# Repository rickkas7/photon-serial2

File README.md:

# Serial2 on the Particle Photon

Normally, the Particle Photon has one UART hardware serial port (Serial1) and the USB serial port (Serial). There is another hardware UART serial port (Serial2), but getting to it is a pain. I don't recommend using it. 

Serial2 shares the same pins as the RGB status LED. This means that you have to disable to status LED. This will make debugging a pain in the future. If your code is running, you can mirror the status LED on another LED. Unfortunately that doesn't work when your code is not running, which is really when you need the status LED. Plus, you need to do soldering and remove some SMD resistors from the Photon. 

Anyway, you have been warned. Here we go!

## Making bottom connections 

Here's the bottom of the Photon (USB connector on the right).

You need to make connections to pins 28 and 29 (the serial port) and optionally pin 27 (red LED). By doing all three, you can attach an external RGB LED to these pins, which may be helpful for debugging.

I used three female header sockets. You may prefer to use a different type of connector. Also, I decided that the pins should be mounted on the USB side, to keep the metal from the connectors out of the keep-away zone under the antenna.

Here is is after soldering the leads in place:

- White Wire: 28 Green LED/TX
- Purple Wire: 29 Blue LED/RX
- Brown Wire: 27 Red LED

I used epoxy to glue the headers in place. This was more difficult and messier than I anticipated.

There is a much better way of doing this at the end of the document!

## Testing out the LED

One advantage of making all three connections is that you can verify your wiring by using an external common anode RGB LED. I used [this one from Adafruit](https://www.adafruit.com/products/159) but any common anode LED should work.

Left to right when positioned as shown above (flat side on right, longest lead is second from right):

- 4 = Blue
- 3 = Green
- 1 = Common Anode (longest lead)
- 2 = Red

Here is the external LED connected to the pins:

- Orange wire: Photon pin 28 to LED pin 4, blue
- White wire: Photon pin 29 to LED pin 3, green
- Yellow wire: Photon pin 27 to LED pin 2, red

There is also a 330 ohm resistor on each of the 3 cathodes.

With any luck, everything will be working properly, verifying the connections on the bottom are good and you didn't break anything.

## Disconnecting the built-in LED

Here's where things get more destructive. You need to disconnect the built-in RGB LED when using Serial2 because otherwise the TX and RX pins will be connected via the LED, and data corruption will likely result. The easiest and safest way to do this is to remove the 3 current limiting resistors R1, R2, and R7.

If you have an SMD hot air rework station, it would be easy to remove these resistors.

In theory you should be able to remove them with a soldering iron. I had trouble doing this, so I used a drill press with a 1/16" bit and the stop set to make sure I didn't drill into the circuit board. 

Here's the Photon with the resistors removed:

It took a few tries, but you can tell you did it successfully when you boot up and the status LED doesn't light up. 

## Using the alternate status LED (0.6.1 and later)

This should set the alternate status LED to work automatically from the boot loader with 0.6.1 and later. 

```
STARTUP(RGB.mirrorTo(D2, D3, A4, true, true));

void setup() {
}

void loop() {
}
```

## Using the alternate status LED (0.6.0 and earlier)

To use the status LED on different pins, you must choose other pins that have PWM support. I selected:

- D2: Red LED (yellow wire)
- D3: Green (orange wire)
- A4: Blue (white wire)

The documentations for [tone](https://docs.particle.io/reference/firmware/photon/#tone-) more details of which pins you can use. I purposely avoided D0/D1 since I2C can be handy, and TX/RX since why would to go through the insanity if you didn't need both UART serial ports.

And here's the sample code to test out the LED on the new pins:

```
#include "Particle.h"

SYSTEM_THREAD(ENABLED);

// These must be PWM compatible pins, all on different timers. See:
// https://docs.particle.io/reference/firmware/photon/#tone-
const int RED_PIN = D2;
const int GREEN_PIN = D3;
const int BLUE_PIN = A4;

// LED is a common anode RGB LED, like:
// https://www.adafruit.com/products/159
//
// (    LED   ]  <- flattened side
//  |  |  |  |
//  4  |  |  |
//     3  |  2
//        1
// Left to right:
// 4 = Blue
// 3 = Green
// 1 = Common Anode (longest lead)
// 2 = Red

// Forward declaration
void ledChangeHandler(uint8_t r, uint8_t g, uint8_t b);

void setup() {
	Serial.begin(9600);

	pinMode(RED_PIN, OUTPUT);
	pinMode(GREEN_PIN, OUTPUT);
	pinMode(BLUE_PIN, OUTPUT);
	RGB.onChange(ledChangeHandler);

}

void loop() {
}

void ledChangeHandler(uint8_t r, uint8_t g, uint8_t b) {
	analogWrite(RED_PIN, 255 - r);
	analogWrite(GREEN_PIN, 255 - g);
	analogWrite(BLUE_PIN, 255 - b);
}

```

## Using the serial port

Of course the whole reason to do this was to use the Serial2 port. 

When you're looking at the modified Photon from the USB port side for serial port use: 

- Serial2 TX (green wire)
- Serial2 RX (blue wire)
- no connection

Here's the code that I ran on the left (modified) Photon:

```
#include "Particle.h"

#include "Serial2/Serial2.h"

SYSTEM_THREAD(ENABLED);

// These must be PWM compatible pins, all on different timers. See:
// https://docs.particle.io/reference/firmware/photon/#tone-
const int RED_PIN = D2;
const int GREEN_PIN = D3;
const int BLUE_PIN = A4;
const size_t READ_BUF_SIZE = 64;

// Forward declaration
void ledChangeHandler(uint8_t r, uint8_t g, uint8_t b);
void processBuffer();

// Global variables
char readBuf[READ_BUF_SIZE];
size_t readBufOffset = 0;

void setup() {
	Serial.begin(9600);
	Serial2.begin(9600);

	pinMode(RED_PIN, OUTPUT);
	pinMode(GREEN_PIN, OUTPUT);
	pinMode(BLUE_PIN, OUTPUT);
	RGB.onChange(ledChangeHandler);
}

void loop() {
	// Read data from serial
	while(Serial2.available()) {
		if (readBufOffset < READ_BUF_SIZE) {
			char c = Serial2.read();
			if (c != '\n') {
				// Add character to buffer
				readBuf[readBufOffset++] = c;
			}
			else {
				// End of line character found, process line
				readBuf[readBufOffset] = 0;
				processBuffer();
				readBufOffset = 0;
			}
		}
		else {
			readBufOffset = 0;
		}
	}

}

void processBuffer() {
	int receivedValue = atoi(readBuf);

	// This program just increments the value sent by the Photon and returns it
	Serial2.printf("%d\n", receivedValue + 1);
}

void ledChangeHandler(uint8_t r, uint8_t g, uint8_t b) {
	// For a common anode LED, you need to use
	analogWrite(RED_PIN, 255 - r);
	analogWrite(GREEN_PIN, 255 - g);
	analogWrite(BLUE_PIN, 255 - b);
}
```

And the Photon Test2 on the right:

```
#include "Particle.h"

// Constants
const unsigned long SEND_INTERVAL_MS = 2000;
const size_t READ_BUF_SIZE = 64;

// Forward declarations
void processBuffer();

// Global variables
int counter = 0;
unsigned long lastSend = 0;

char readBuf[READ_BUF_SIZE];
size_t readBufOffset = 0;

void setup() {
	Serial.begin(9600);

	// Serial1 RX is connected to other Photon TX
	// Serial2 TX is connected to other Photon RX
	// Photon GND is connected to other Photon GND
	Serial1.begin(9600);
}

void loop() {
	if (millis() - lastSend >= SEND_INTERVAL_MS) {
		lastSend = millis();

		Serial1.printlnf("%d", ++counter);
		Serial.printlnf("Sent to other Photon: %d", counter);
	}

	// Read data from serial
	while(Serial1.available()) {
		if (readBufOffset < READ_BUF_SIZE) {
			char c = Serial1.read();
			if (c != '\n') {
				// Add character to buffer
				readBuf[readBufOffset++] = c;
			}
			else {
				// End of line character found, process line
				readBuf[readBufOffset] = 0;
				processBuffer();
				readBufOffset = 0;
			}
		}
		else {
			Serial.println("readBuf overflow, emptying buffer");
			readBufOffset = 0;
		}
	}

}

void processBuffer() {
	Serial.printlnf("Received from other Photon: %s", readBuf);
}
```

And the output from Test2:

```
particle serial monitor /dev/cu.usbmodemFD1141
Opening serial monitor for com port: "/dev/cu.usbmodemFD1141"
Sent to other Photon: 1
Received from other Photon: 2
Sent to other Photon: 2
Received from other Photon: 3
Sent to other Photon: 3
Received from other Photon: 4
Sent to other Photon: 4
Received from other Photon: 5
Sent to other Photon: 5
Received from other Photon: 6
```

## Better way of making bottom connections

There is a much better way of making the bottom connections, as well. Using the "no headers" version of the Photon, it can be surface mounted on a printed circuit board:

This is just a test board that exposes all of the bottom connections as well as the standard Photon pins. This works best if you have a reflow oven to bake the Photon onto the circuit board, as it's impossible to hand-solder to the bottom pads in the SMT configuration.

The standard Eagle footprints for the SMT version of the Electron include the bottom pads. The schematic and board file for this board are included in the "eagle" directory.

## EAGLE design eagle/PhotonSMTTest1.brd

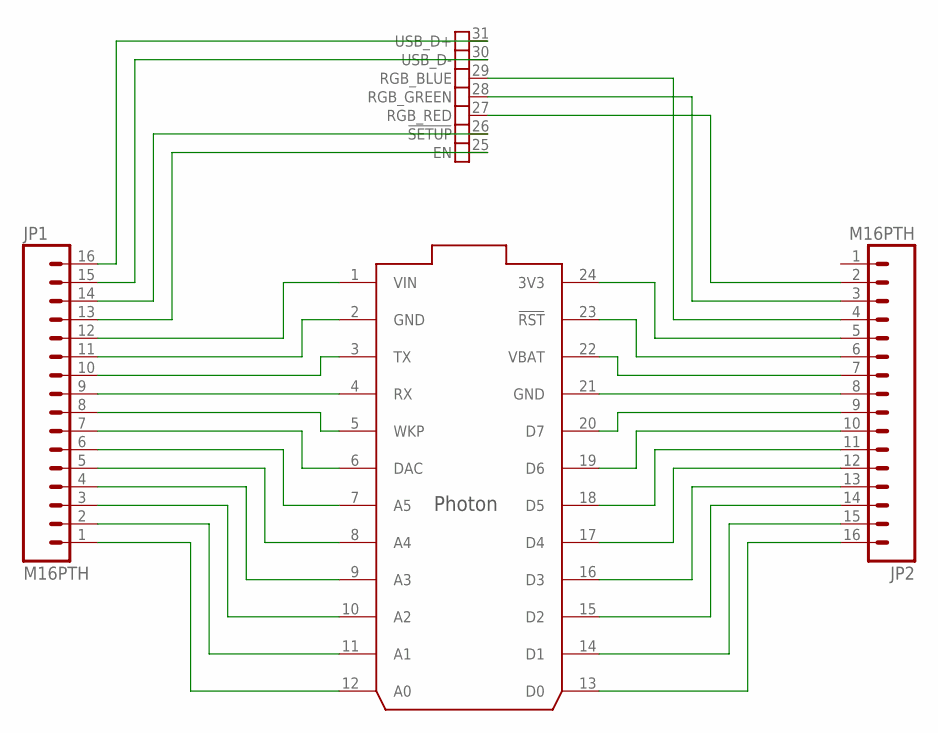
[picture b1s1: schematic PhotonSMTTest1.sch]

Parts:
.: PHOTON_SMD
JP1, JP2: M16PTH; 1X16

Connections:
GND: ..2 (GND), ..21 (GND), JP1.11, JP2.8
unnamed: ..1 (VIN), JP1.12
unnamed: ..31 (USB_D+), JP1.16
unnamed: ..3 (TX), JP1.10
unnamed: ..4 (RX), JP1.9
unnamed: ..6 (DAC), JP1.7
unnamed: ..8 (A4), JP1.5
unnamed: ..7 (A5), JP1.6
unnamed: ..5 (WKP), JP1.8
unnamed: ..9 (A3), JP1.4
unnamed: ..10 (A2), JP1.3
unnamed: ..11 (A1), JP1.2
unnamed: ..12 (A0), JP1.1
unnamed: ..24 (3V3), JP2.5
unnamed: ..23 (!RST), JP2.6
unnamed: ..22 (VBAT), JP2.7
unnamed: ..30 (USB_D-), JP1.15
unnamed: ..20 (D7), JP2.9
unnamed: ..19 (D6), JP2.10
unnamed: ..18 (D5), JP2.11
unnamed: ..17 (D4), JP2.12
unnamed: ..16 (D3), JP2.13
unnamed: ..15 (D2), JP2.14
unnamed: ..14 (D1), JP2.15
unnamed: ..13 (D0), JP2.16
unnamed: ..29 (RGB_BLUE), JP2.4
unnamed: ..28 (RGB_GREEN), JP2.3
unnamed: ..27 (RGB_RED), JP2.2
unnamed: ..26 (!SETUP), JP1.14
unnamed: ..25 (EN), JP1.13

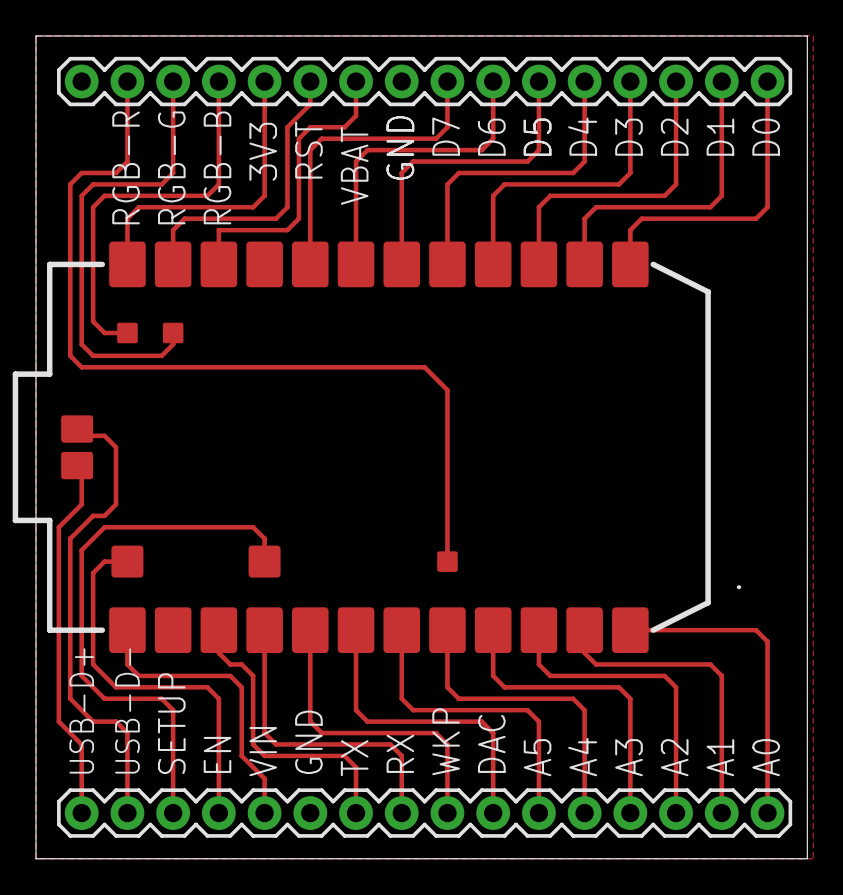
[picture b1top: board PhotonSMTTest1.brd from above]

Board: 2 copper layers, 42.9 x 45.7 mm, 3 parts (0 on the bottom side), 30 nets.

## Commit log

2016-10-29 initial checkin
2016-10-30 fix incorrect picture for alt led
2017-09-18 Add SMT instructions and files

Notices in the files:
parts and their libraries:
Particle-Devices: Licensing: Designed by Particle.
